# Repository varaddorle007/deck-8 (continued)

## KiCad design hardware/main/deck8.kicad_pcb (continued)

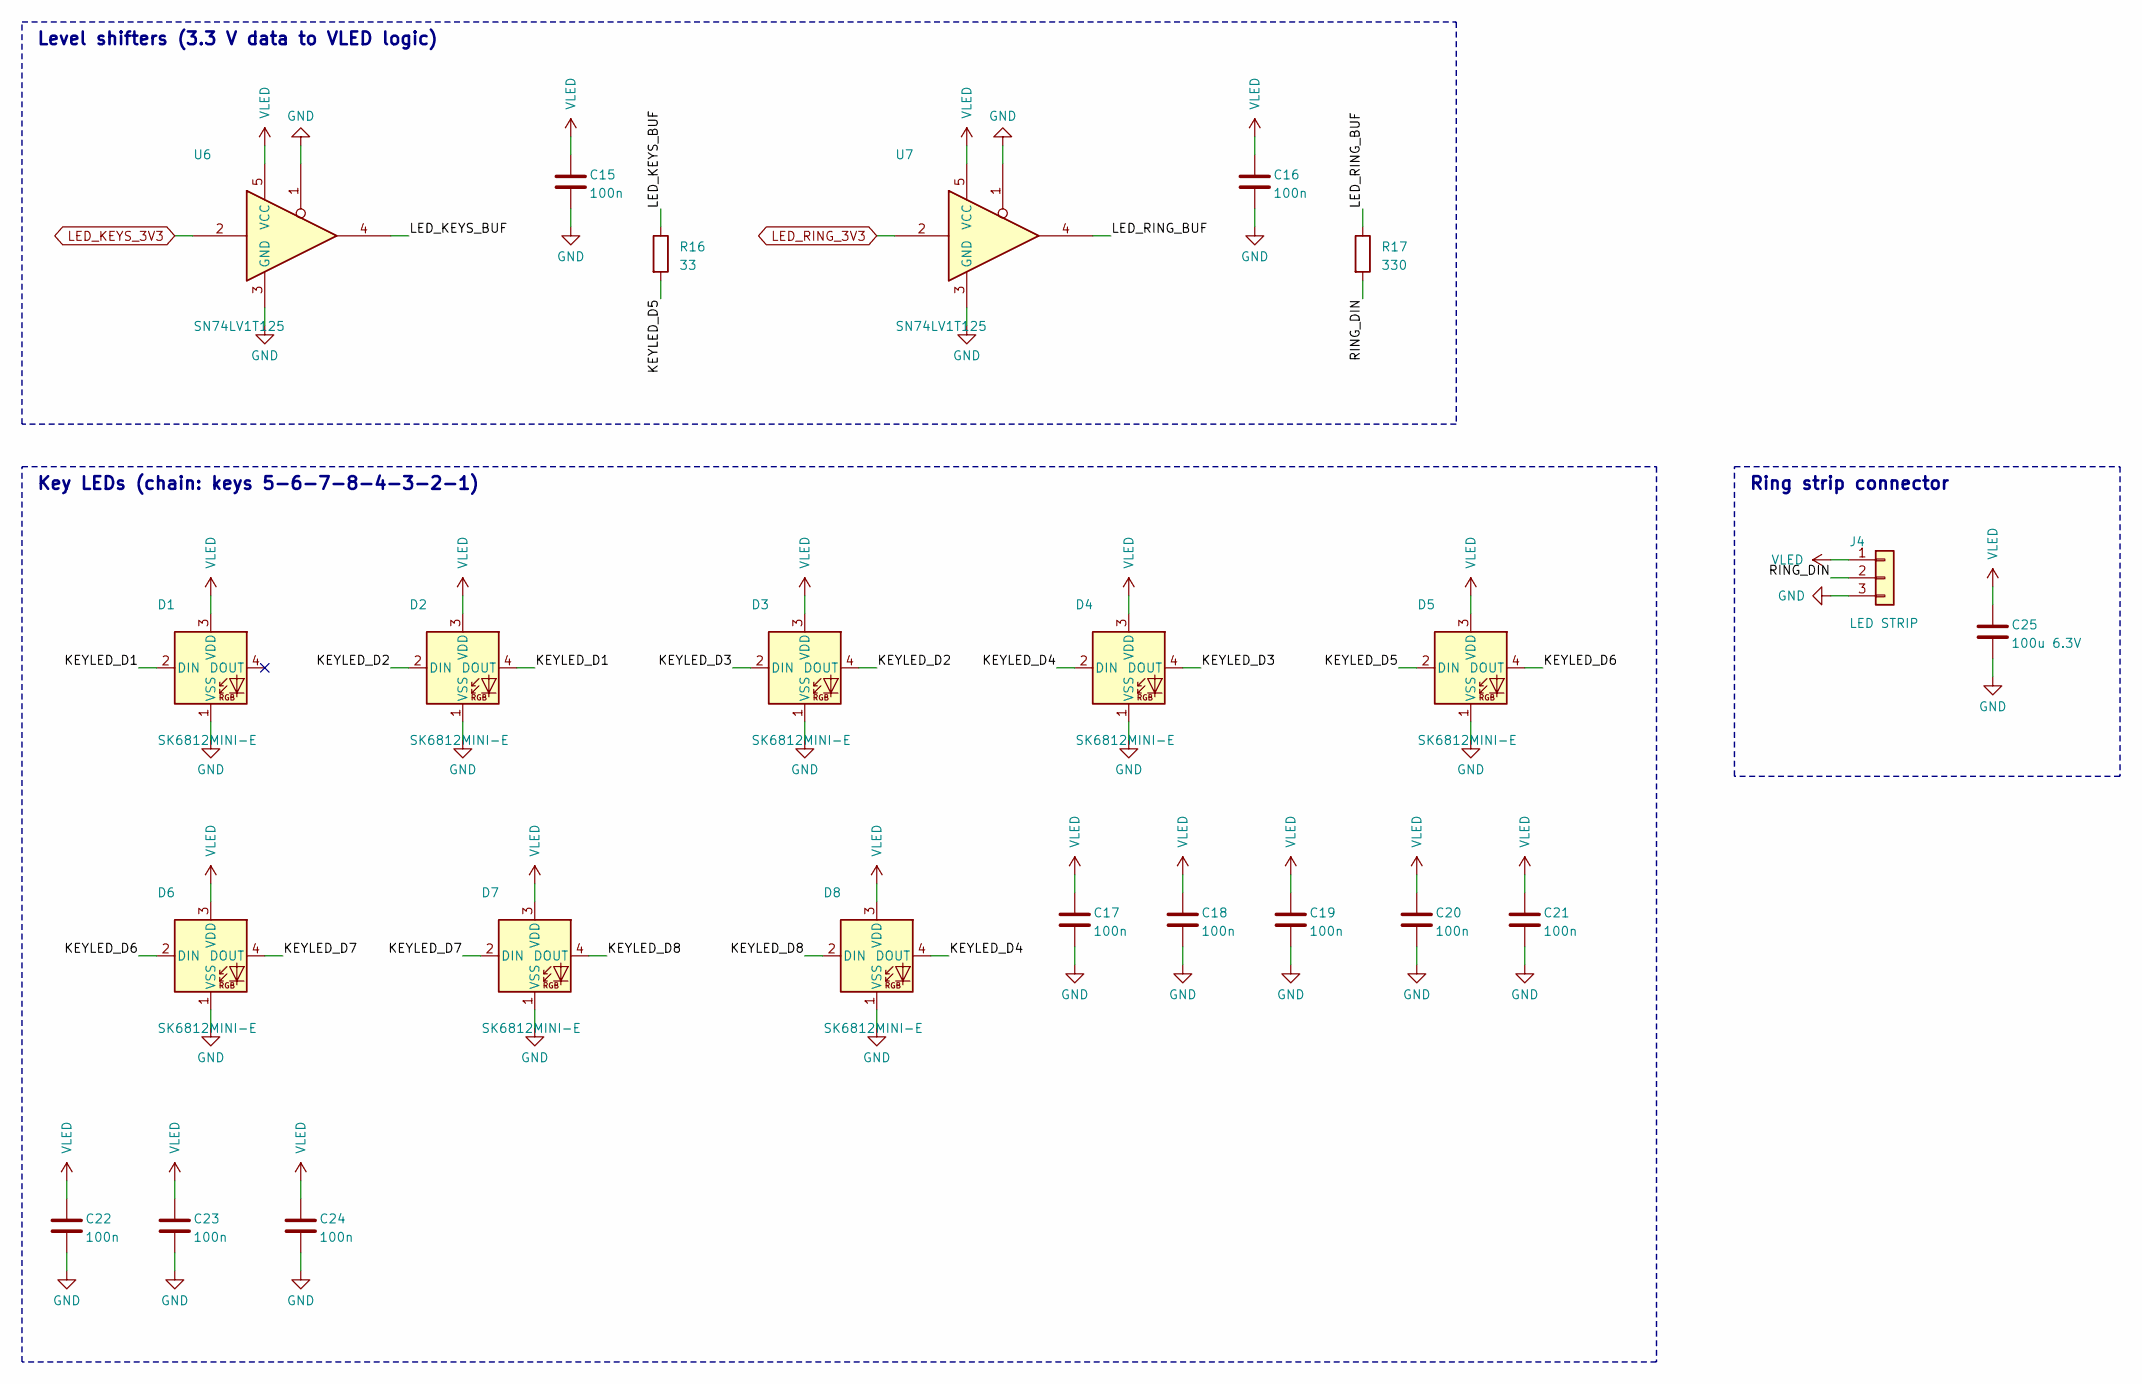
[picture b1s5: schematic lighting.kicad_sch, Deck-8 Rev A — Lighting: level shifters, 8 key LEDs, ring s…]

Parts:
C15, C16, C17, C18, C19, C20, C21, C22, C23, C24: 100n; C_0603_1608Metric; MPN CC0603KRX7R9BB104 (50 V X7R); LCSC C14663
C25: 100u 6.3V; C_1206_3216Metric; MPN CL31A107MQHNNNE (1206, 6.3 V X5R); LCSC C15008
D1, D2, D3, D4, D5, D6, D7, D8: SK6812MINI-E; LED_SK6812MINI-E_3.2x2.8mm_P1.5mm_ReverseMount; MPN OPSCO SK6812MINI-E; LCSC C5149201
J4: LED STRIP; JST_SH_SM03B-SRSS-TB_1x03-1MP_P1.00mm_Horizontal; MPN Joint Tech A1001WR-S-03P (JST SH compat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; LCSC C371509
R16: 33; R_0603_1608Metric; MPN UNI-ROYAL 0603WAF330JT5E; LCSC C23140
R17: 330; R_0603_1608Metric; MPN UNI-ROYAL 0603WAF3300T5E; LCSC C23138
U6, U7: SN74LV1T125; SOT-23-5; MPN TI SN74LV1T125DBVR; LCSC C473338

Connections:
/Lighting/KEYLED_D1: D1.2 (DIN), D2.4 (DOUT)
/Lighting/KEYLED_D2: D2.2 (DIN), D3.4 (DOUT)
/Lighting/KEYLED_D3: D3.2 (DIN), D4.4 (DOUT)
/Lighting/KEYLED_D4: D4.2 (DIN), D8.4 (DOUT)
/Lighting/KEYLED_D5: D5.2 (DIN), R16.2
/Lighting/KEYLED_D6: D5.4 (DOUT), D6.2 (DIN)
/Lighting/KEYLED_D7: D6.4 (DOUT), D7.2 (DIN)
/Lighting/KEYLED_D8: D7.4 (DOUT), D8.2 (DIN)
/Lighting/LED_KEYS_BUF: R16.1, U6.4
/Lighting/LED_RING_BUF: R17.1, U7.4
/Lighting/RING_DIN: J4.2, R17.2
GND: C15.2, C16.2, C17.2, C18.2, C19.2, C20.2, C21.2, C22.2, C23.2, C24.2, C25.2, D1.1 (VSS), D2.1 (VSS), D3.1 (VSS), D4.1 (VSS), D5.1 (VSS), D6.1 (VSS), D7.1 (VSS), D8.1 (VSS), J4.3, U6.1, U6.3 (GND), U7.1, U7.3 (GND); also elsewhere on the board
LED_KEYS_3V3: U6.2; also elsewhere on the board
LED_RING_3V3: U7.2; also elsewhere on the board
VLED: C15.1, C16.1, C17.1, C18.1, C19.1, C20.1, C21.1, C22.1, C23.1, C24.1, C25.1, D1.3 (VDD), D2.3 (VDD), D3.3 (VDD), D4.3 (VDD), D5.3 (VDD), D6.3 (VDD), D7.3 (VDD), D8.3 (VDD), J4.1, U6.5 (VCC), U7.5 (VCC); also elsewhere on the board

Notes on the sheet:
Level shifters (3.3 V data to VLED logic)
Key LEDs (chain: keys 5-6-7-8-4-3-2-1)
Ring strip connector

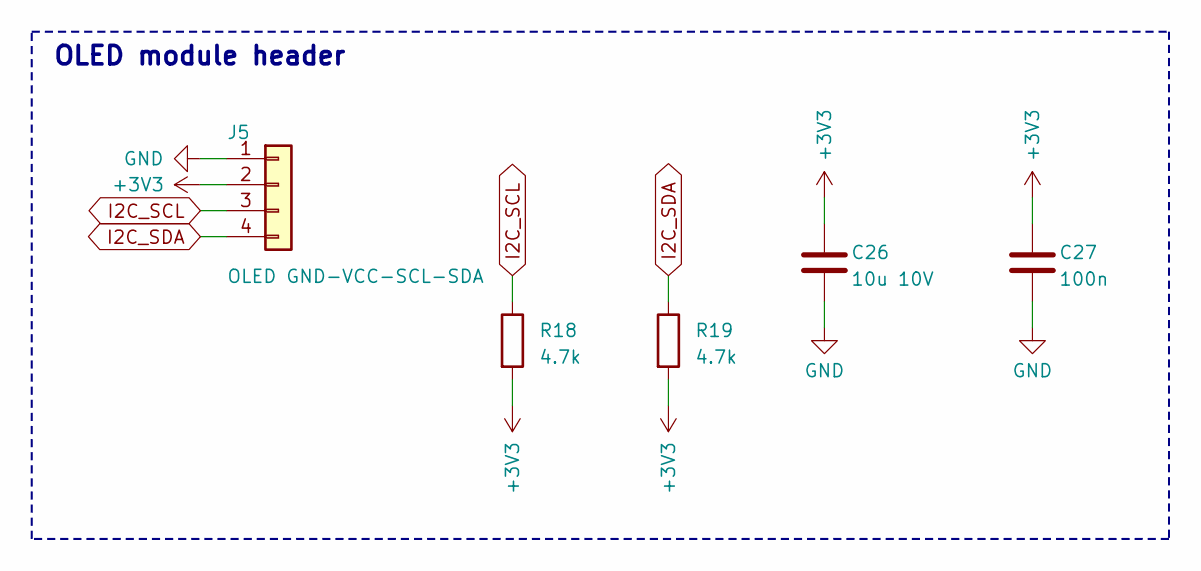
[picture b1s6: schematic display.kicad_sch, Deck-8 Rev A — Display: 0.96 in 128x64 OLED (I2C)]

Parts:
C26: 10u 10V; C_0603_1608Metric; MPN CL10A106KP8NNNC (10 V X5R); LCSC C19702
C27: 100n; C_0603_1608Metric; MPN CC0603KRX7R9BB104 (50 V X7R); LCSC C14663
J5: OLED GND-VCC-SCL-SDA; PinHeader_1x04_P2.54mm_Vertical; MPN 0.96 in 128x64 I2C OLED module (SSD1306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
R18, R19: 4.7k; R_0603_1608Metric; MPN UNI-ROYAL 0603WAF4701T5E; LCSC C23162

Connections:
+3V3: C26.1, C27.1, J5.2, R18.2, R19.2; also elsewhere on the board
GND: C26.2, C27.2, J5.1; also elsewhere on the board
I2C_SCL: J5.3, R18.1; also elsewhere on the board
I2C_SDA: J5.4, R19.1; also elsewhere on the board

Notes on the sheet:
OLED module header

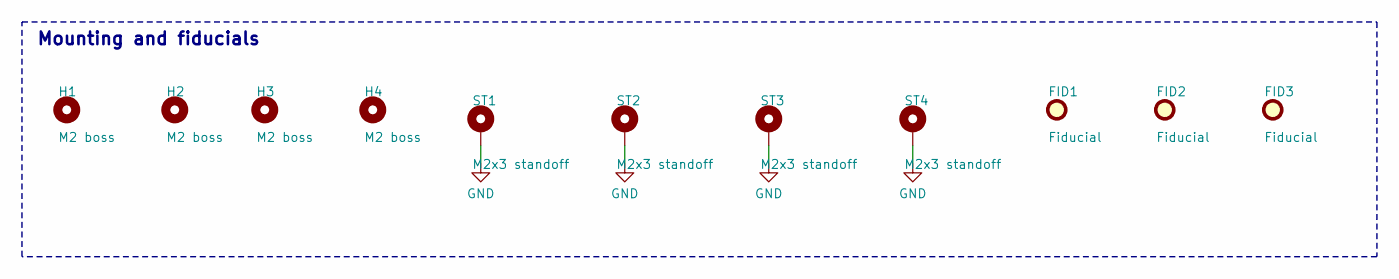
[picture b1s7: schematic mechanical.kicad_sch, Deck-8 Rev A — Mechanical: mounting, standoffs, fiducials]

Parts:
FID1, FID2, FID3: Fiducial; Fiducial_1mm_Mask2mm
H1, H2, H3, H4: M2 boss; MountingHole_2.2mm_M2
ST1, ST2, ST3, ST4: M2x3 standoff; Mounting_Wuerth_WA-SMSI-M2_H3mm_9774030243; MPN Wurth 9774030243

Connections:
GND: ST1.1, ST2.1, ST3.1, ST4.1; also elsewhere on the board

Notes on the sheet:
Mounting and fiducials

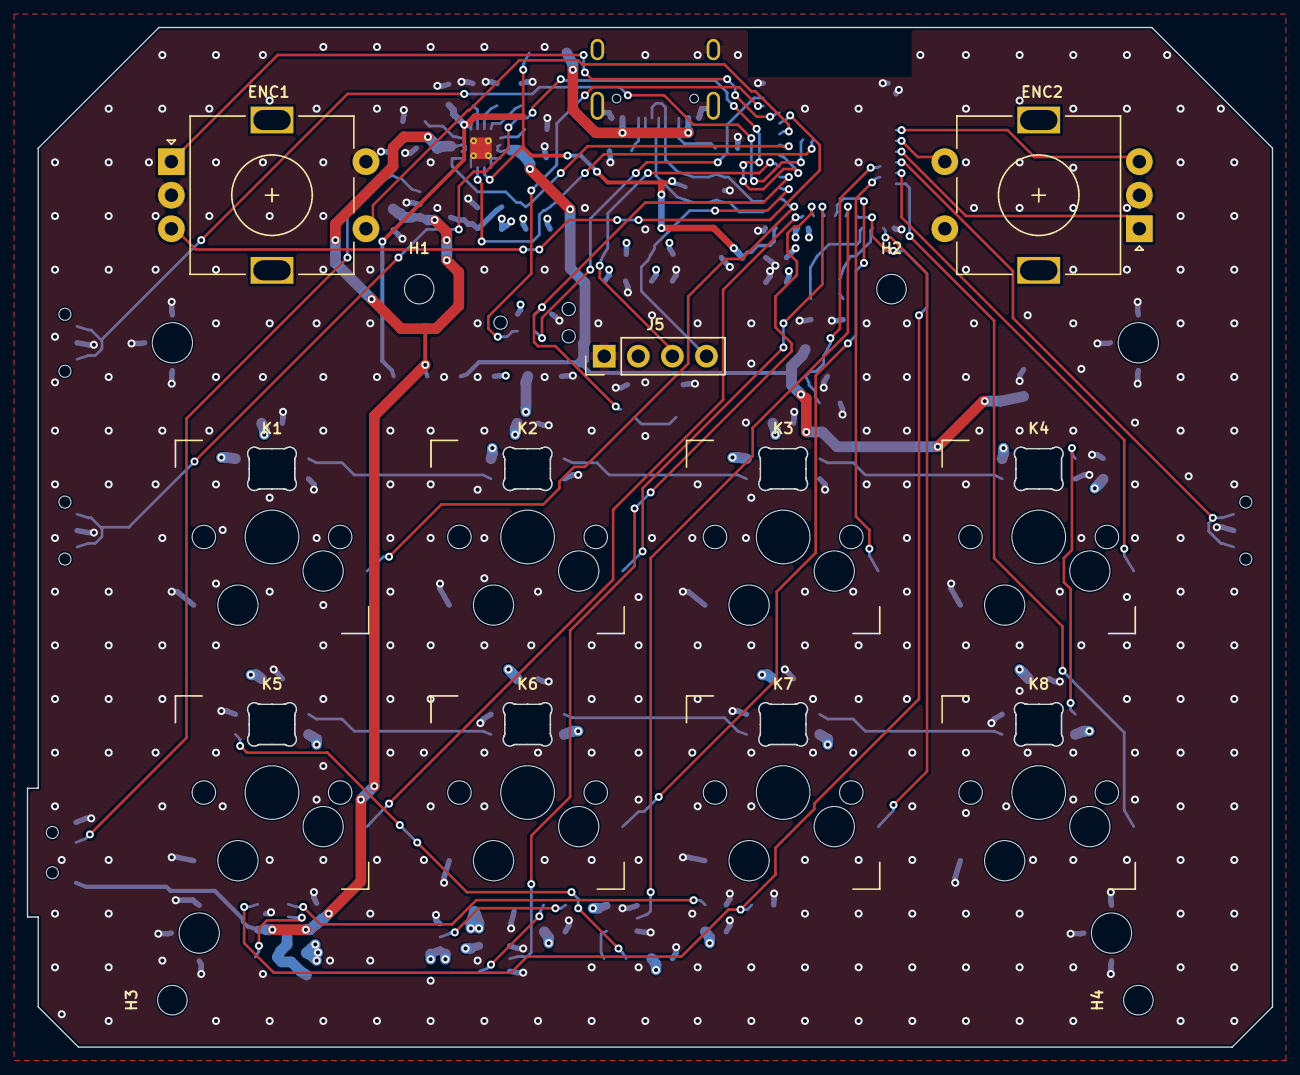
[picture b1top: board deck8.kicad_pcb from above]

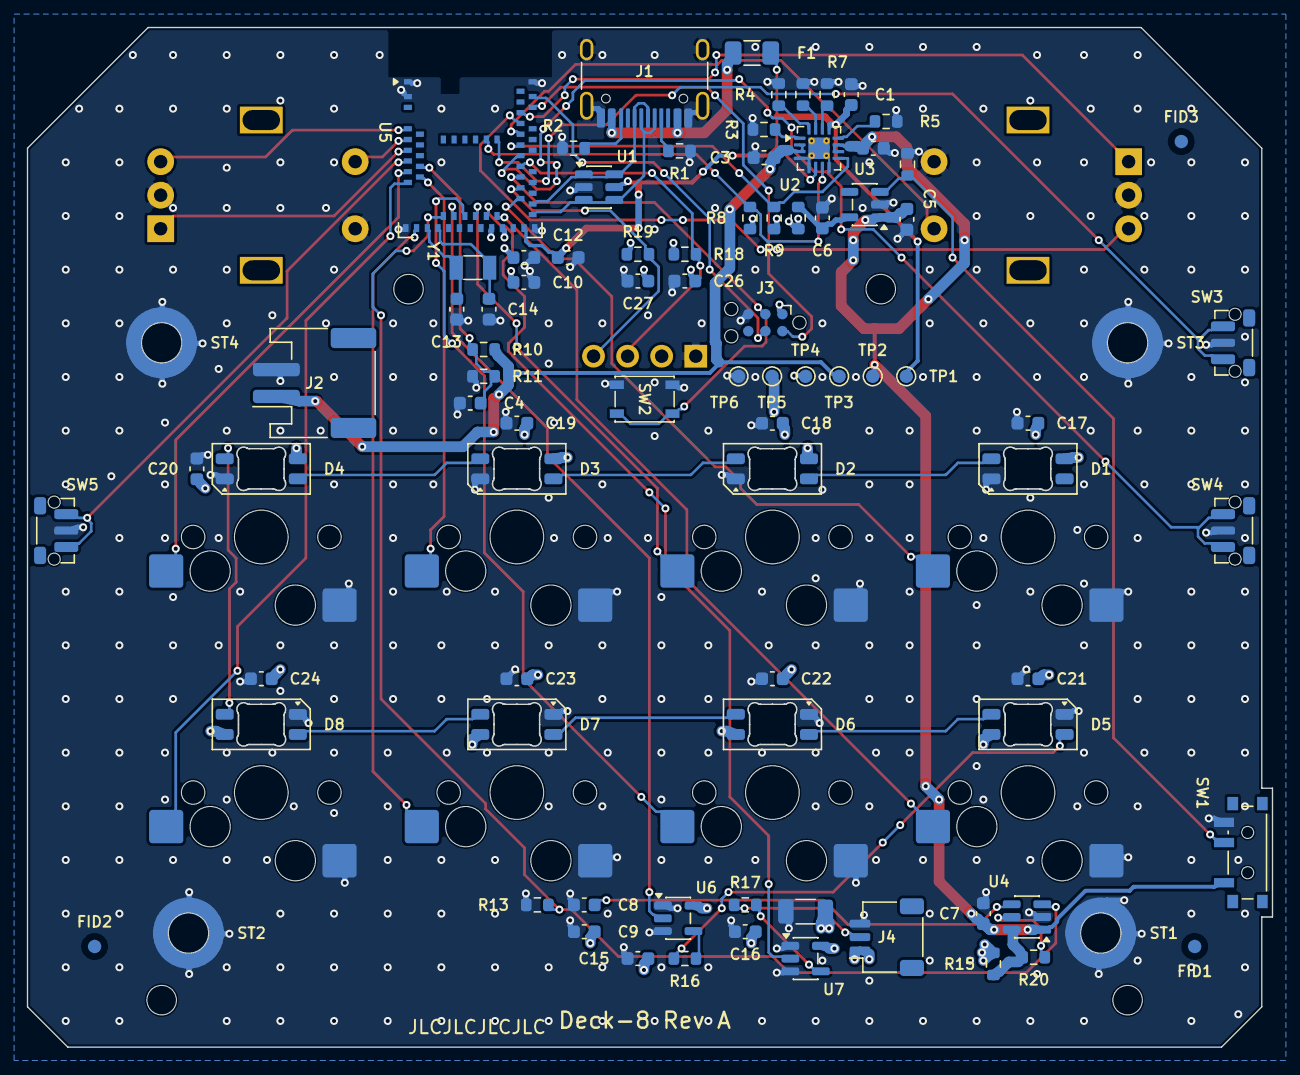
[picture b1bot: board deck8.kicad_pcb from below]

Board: 4 copper layers, 92.8 x 76.0 mm, 101 parts (86 on the bottom side), 62 nets.

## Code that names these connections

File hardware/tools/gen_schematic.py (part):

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# matching of free pads to destinations on the Rev A placement, which also keeps the escapes from crossing.
# West-going signals use the inner and centre pads, which drop a via straight to the free top layer; the outer
# west pads could only leave into the gap beside the USB ESD part. The outer south pads P0.04/P0.06/P0.08/P1.09
# stay free because the crystal lines run under them. I2C and LED data are on P0 (full-speed) pins, BAT_SENSE
# on AIN0.
MCU_PINS = {
    "P0.14": "KEY1", "P1.08": "KEY2", "P0.28": "KEY3", "P0.31": "KEY4",
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             by_name={"VIN": "VSYS", "GND": "GND", "ON": "LED_EN", "CT": "LED_CT", "QOD": "LED_QOD", "VOUT": "VLED_SW"},
             mpn="TI TPS22917DBVR", lcsc="C2681320"),
        R("R20", "0R", "LED_QOD", "VLED_SW", note="quick output discharge; a resistor here slows it"),
        C("C7", "1u 10V", "VSYS"), C("C8", "1n", "LED_CT", note="slew rate, keeps VSYS from dipping"),
        R("R13", "100k", "LED_EN", "GND", note="LEDs off while the MCU is off"),
        R("R15", "0R", "VLED_SW", "VLED", note="lift to measure LED current"),
        C("C9", "10u 10V", "VLED"), flag("#FLG04", "VLED"),
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    ain = {"P0.02": 0, "P0.03": 1, "P0.04": 2, "P0.05": 3, "P0.28": 4, "P0.29": 5, "P0.30": 6, "P0.31": 7}
    keys = " ".join(pin[f"KEY{i}"] for i in range(1, 9))
    unused = " ".join(sorted(k for k, v in MCU_PINS.items() if v is None and k.startswith("P")))
    return (f"MCU GPIO: keys 1-8 {keys} | L1 {pin['BTN_L1']} L2 {pin['BTN_L2']} SYS {pin['BTN_SYS']} | "
            f"knob A {pin['ENCA_A']}/{pin['ENCA_B']} sw {pin['ENCA_SW']} | knob B {pin['ENCB_A']}/{pin['ENCB_B']} "
            f"sw {pin['ENCB_SW']}\n"
            f"          I2C SDA {pin['I2C_SDA']} SCL {pin['I2C_SCL']} | LED ring {pin['LED_RING_3V3']}, keys "
            f"{pin['LED_KEYS_3V3']} (SPI MOSI; spare SCK pins are unconnected) | LED_EN {pin['LED_EN']} | "
            f"BAT_SENSE {pin['BAT_SENSE']} (AIN{ain[pin['BAT_SENSE']]}) | CHG_N {pin['CHG_N']} PGOOD_N {pin['PGOOD_N']} | "
            f"reset P0.18 | LFXO P0.00/P0.01\n"
            f"Unused, no-connect: {unused} (P0.09/P0.10 are NFC).\n"
            f"Key LED chain: keys {'-'.join(str(n) for n in LED_CHAIN)}; the back-row LEDs are turned 180 deg.")
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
